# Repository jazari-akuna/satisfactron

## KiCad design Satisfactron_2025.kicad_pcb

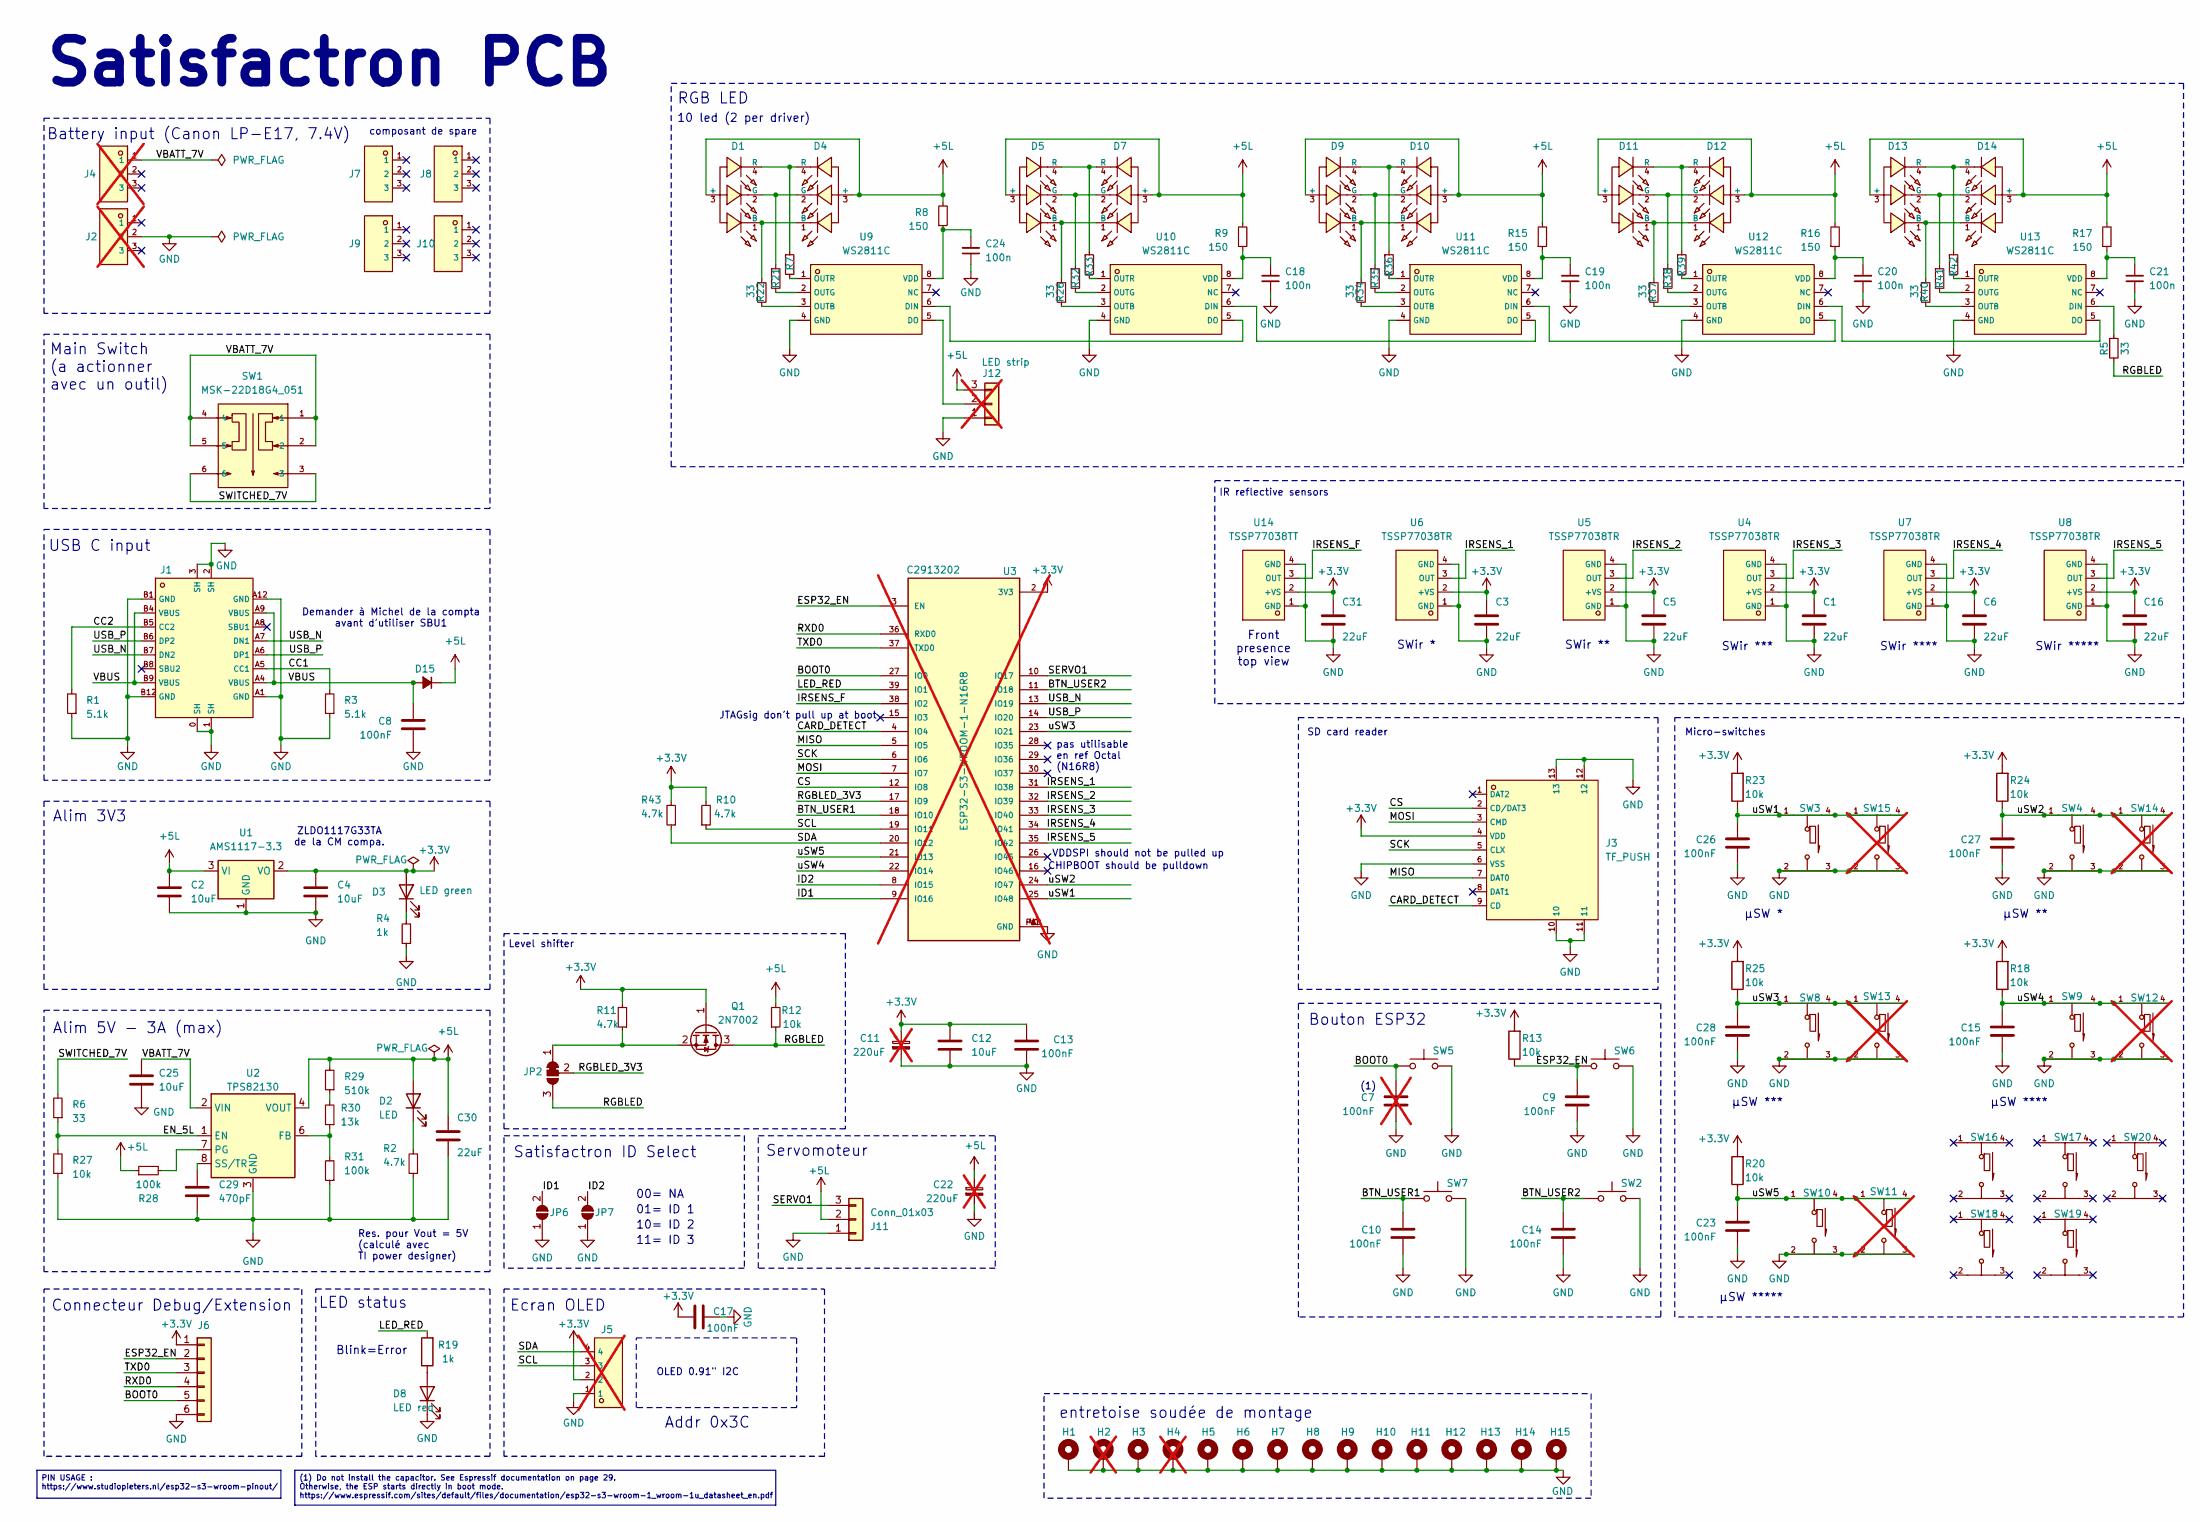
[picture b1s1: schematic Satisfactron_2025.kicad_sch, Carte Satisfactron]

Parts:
C1, C3, C5, C6, C16, C30, C31: 22uF; C_0805_2012Metric; LCSC C45783
C2, C4, C12, C25: 10uF; C_0805_2012Metric; LCSC C440198
C7: 100nF; C_0603_1608Metric_Pad1.08x0.95mm_HandSolder; LCSC C14663; not fitted
C8, C9, C10, C13, C14, C15, C17, C23, C26, C27, C28: 100nF; C_0603_1608Metric_Pad1.08x0.95mm_HandSolder; LCSC C14663
C11, C22: 220uF; C_Radial_D6.3mm_H11.0mm_P2.50mm; not fitted
C18, C19, C20, C21, C24: 100n; C_0603_1608Metric_Pad1.08x0.95mm_HandSolder; LCSC C14663
C29: 470pF; C_0603_1608Metric; LCSC C1620
D1, D4, D5, D7, D9, D10, D11, D12, D13, D14: XL-3210RGBC-YG; LED-ARRAY-SMD_HS-1204-RGB; LCSC C965884
D2: LED; LED_0603_1608Metric; LCSC C2290
D3: LED green; LED_0603_1608Metric; LCSC C2290
D8: LED red; LED_0603_1608Metric; LCSC C2286
D15: 1N4148W; D_SOD-123F; LCSC C81598
H1, H3, H5, H6, H7, H8, H9, H10, H11, H12, H13, H14, H15: SMTSO3040CTJ; SMD-1_BD5.5-D4.0; LCSC C2915635
H2, H4: SMTSO3040CTJ; SMD-1_BD5.5-D4.0; LCSC C2915635; not fitted
J1: USB-TYPE-C-018; USB-C_SMD-TYPE-C-31-M-12; LCSC C2927038
J2, J4: GT-BTP30002-0350B-019B; CONN-SMD_GT-BTP30002-0350B-019B; LCSC C41378766; not fitted
J3: TF_PUSH; TF-SMD_TF-PUSH; LCSC C393941
J5: PZ254V-11-04P_C2691448; Waveshare_screen_0.9; LCSC C2691448; not fitted
J6: Conn_01x06; PinHeader_1x06_P2.54mm_Vertical
J7, J8, J9, J10: GT-BTP30002-0350B-019B; CONN-SMD_GT-BTP30002-0350B-019B; LCSC C41378766
J11: Conn_01x03; PinHeader_1x03_P2.54mm_Vertical
J12: LED strip; PinHeader_1x03_P2.54mm_Vertical; not fitted
JP2: SolderJumper_3_Bridged12; SolderJumper-3_P1.3mm_Bridged12_RoundedPad1.0x1.5mm
JP6: ID1; SolderJumper-2_P1.3mm_Open_RoundedPad1.0x1.5mm
JP7: ID2; SolderJumper-2_P1.3mm_Open_RoundedPad1.0x1.5mm
Q1: 2N7002; SOT-23_Handsoldering; LCSC C8545
R1, R3: 5.1k; R_0603_1608Metric; LCSC C23186
R2, R10, R11, R43: 4.7k; R_0603_1608Metric; LCSC C23162
R4: 1k; R_0603_1608Metric; LCSC C21190
R5, R6, R7, R21, R22, R26, R32, R33, R34, R35, R36, R37, R38, R39, R40, R41, R42: 33; R_0603_1608Metric; LCSC C23140
R8, R9, R15, R16, R17: 150; R_0603_1608Metric; LCSC C22808
R12, R27: 10k; R_0603_1608Metric; LCSC C25804
R13, R18, R20, R23, R24, R25: 10k; R_0603_1608Metric_Pad0.98x0.95mm_HandSolder; LCSC C25804
R19: 1k; R_0603_1608Metric_Pad0.98x0.95mm_HandSolder; LCSC C21190
R28, R31: 100k; R_0603_1608Metric; LCSC C25803
R29: 510k; R_0603_1608Metric; LCSC C23192
R30: 13k; R_0603_1608Metric; LCSC C22797
SW1: MSK-22D18G4_051; SW-TH_HX-MSK-22D18G4-051; LCSC C7507433
SW2, SW5, SW6, SW7: TS-1088-AR02016; SW-SMD_L3.9-W3.0-P4.45; LCSC C720477
SW3, SW4, SW8, SW9, SW10, SW16, SW17, SW18, SW19, SW20: SPVN310101; SW-SMD_SPVN310101; LCSC C255568
SW11, SW12, SW13, SW14, SW15: SPVN310101; SW-SMD_SPVN310101; LCSC C255568; not fitted
U1: AMS1117-3.3; SOT-223-3_TabPin2; LCSC C6186
U2: TPS82130; USIP-8_L3.0-W2.8-P0.65-TL-EP; LCSC C473914
U3: ESP32-S3-WROOM-1-N16R8; WIRELM-SMD_ESP32-S3-WROOM-1; PARTREV v1.0; LCSC C2913202; not fitted
U4, U5, U6, U7, U8: TSSP77038TR; SENSOR-SMD_TSOP75238TR; LCSC C499566
U9, U10, U11, U12, U13: WS2811C; SOP-8_L4.9-W3.9-P1.27-LS6.0-BL; LCSC C2920043
U14: TSSP77038TT; Top-view-TSSP770_SMD_TSOP75238TR; LCSC C3742899

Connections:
+3.3V: C1.1, C3.1, C4.1, C5.1, C6.1, C11.1, C12.1, C13.1, C16.1, C17.1, C31.1, D3.2 (A), J3.4 (VDD), J5.2, J6.1, Q1.1 (G), R10.2, R11.2, R13.2, R18.2, R20.2, R23.2, R24.2, R25.2, R43.2, U1.2 (VO), U3.2 (3V3), U4.2 (+VS), U5.2 (+VS), U6.2 (+VS), U7.2 (+VS), U8.2 (+VS), U14.2 (+VS); also elsewhere on the board
+5L: C2.1, C22.1, C30.1, D1.3 (+), D2.2 (A), D4.3 (+), D5.3 (+), D7.3 (+), D9.3 (+), D10.3 (+), D11.3 (+), D12.3 (+), D13.3 (+), D14.3 (+), D15.1 (K), J11.2, J12.3, R8.2, R9.2, R12.2, R15.2, R16.2, R17.2, R28.1, R29.2, U1.3 (VI), U2.4 (VOUT), U2.5 (VOUT)
/BOOT0: C7.1, J6.5, SW5.1, U3.27 (IO0)
/BTN_USER1: C10.1, SW7.1, U3.18 (IO10)
/BTN_USER2: C14.1, SW2.1, U3.11 (IO18)
/CARD_DETECT: J3.9 (CD), U3.4 (IO4)
/CC1: J1.A5 (CC1), R3.2
/CC2: J1.B5 (CC2), R1.2
/CS: J3.2 (CD/DAT3), U3.12 (IO8)
/EN_5L: R6.1, R27.2, U2.1 (EN)
/ESP32_EN: C9.1, J6.2, R13.1, SW6.1, U3.3 (EN)
/ID1: JP6.2 (B), U3.9 (IO16)
/ID2: JP7.2 (B), U3.8 (IO15)
/IRSENS_1: U3.31 (IO38), U6.3 (OUT)
/IRSENS_2: U3.32 (IO39), U5.3 (OUT)
/IRSENS_3: U3.33 (IO40), U4.3 (OUT)
/IRSENS_4: U3.34 (IO41), U7.3 (OUT)
/IRSENS_5: U3.35 (IO42), U8.3 (OUT)
/IRSENS_F: U3.38 (IO2), U14.3 (OUT); also elsewhere on the board
/LED_RED: R19.2, U3.39 (IO1)
/MISO: J3.7 (DAT0), U3.5 (IO5)
/MOSI: J3.3 (CMD), U3.7 (IO7)
/RGBLED: JP2.3 (B), Q1.3 (D), R5.2, R12.1
/RGBLED_3V3: JP2.2 (C), U3.17 (IO9)
/RXD0: J6.4, U3.36 (RXD0)
/SCK: J3.5 (CLX), U3.6 (IO6)
/SCL: J5.3, R10.1, U3.19 (IO11)
/SDA: J5.4, R43.1, U3.20 (IO12)
/SERVO1: J11.3, U3.10 (IO17)
/SWITCHED_7V: R6.2, SW1.3, SW1.6
/TXD0: J6.3, U3.37 (TXD0)
/USB_N: J1.A7 (DN1), J1.B7 (DN2), U3.13 (IO19)
/USB_P: J1.A6 (DP1), J1.B6 (DP2), U3.14 (IO20)
/VBATT_7V: C25.1, J4.1, SW1.1, SW1.2, SW1.4, SW1.5, U2.2 (VIN)
/VBUS: C8.1, D15.2 (A), J1.A4 (VBUS), J1.A9 (VBUS), J1.B4 (VBUS), J1.B9 (VBUS)
/uSW1: C26.1, R23.1, SW3.1, SW3.4, SW15.1, SW15.4, U3.25 (IO48)
/uSW2: C27.1, R24.1, SW4.1, SW4.4, SW14.1, SW14.4, U3.24 (IO47)
/uSW3: C28.1, R25.1, SW8.1, SW8.4, SW13.1, SW13.4, U3.23 (IO21)
/uSW4: C15.1, R18.1, SW9.1, SW9.4, SW12.1, SW12.4, U3.22 (IO14)
/uSW5: C23.1, R20.1, SW10.1, SW10.4, SW11.1, SW11.4, U3.21 (IO13)
GND: C1.2, C2.2, C3.2, C4.2, C5.2, C6.2, C7.2, C8.2, C9.2, C10.2, C11.2, C12.2, C13.2, C14.2, C15.2, C16.2, C17.2, C18.1, C19.1, C20.1, C21.1, C22.2, C23.2, C24.1, C25.2, C26.2, C27.2, C28.2, C29.2, C30.2, C31.2, D8.1 (K), H1.1, H2.1, H3.1, H4.1, H5.1, H6.1, H7.1, H8.1, H9.1, H10.1, H11.1, H12.1, H13.1, H14.1, H15.1, J1.0 (SH), J1.1 (SH), J1.2 (SH), J1.3 (SH), J1.A1 (GND), J1.A12 (GND), J1.B1 (GND), J1.B12 (GND), J2.2, J3.6 (VSS), J3.10, J3.11, J3.12, J3.13, J5.1, J6.6, J11.1, J12.1, JP6.1 (A), JP7.1 (A), R1.1, R2.1, R3.1, R4.1, R27.1, R31.1, SW2.2, SW3.2, SW3.3, SW4.2, SW4.3, SW5.2, SW6.2, SW7.2, SW8.2, SW8.3, SW9.2, SW9.3, SW10.2, SW10.3, SW11.2, SW11.3, SW12.2, SW12.3, SW13.2, SW13.3, SW14.2, SW14.3, SW15.2, SW15.3, U1.1 (GND), U2.3 (GND), U2.9 (GND), U3.1 (GND), U3.40 (GND), U3.PAD (GND), U4.1 (GND), U4.4 (GND), U5.1 (GND), U5.4 (GND), U6.1 (GND), U6.4 (GND), U7.1 (GND), U7.4 (GND), U8.1 (GND), U8.4 (GND), U9.4 (GND), U10.4 (GND), U11.4 (GND), U12.4 (GND), U13.4 (GND), U14.1 (GND), U14.4 (GND); also elsewhere on the board
unnamed: D1.1 (B), D4.1 (B), R22.1
unnamed: D1.2 (G), D4.2 (G), R21.1
unnamed: D1.4 (R), D4.4 (R), R7.1
unnamed: D2.1 (K), R2.2
unnamed: D3.1 (K), R4.2
unnamed: D5.1 (B), D7.1 (B), R26.1
unnamed: D5.2 (G), D7.2 (G), R32.1
unnamed: D5.4 (R), D7.4 (R), R33.1
unnamed: D8.2 (A), R19.1
unnamed: D9.1 (B), D10.1 (B), R34.1
unnamed: D9.2 (G), D10.2 (G), R35.1
unnamed: D9.4 (R), D10.4 (R), R36.1
unnamed: D11.1 (B), D12.1 (B), R37.1
unnamed: D11.2 (G), D12.2 (G), R38.1
unnamed: D11.4 (R), D12.4 (R), R39.1
unnamed: D13.1 (B), D14.1 (B), R40.1
unnamed: D13.2 (G), D14.2 (G), R41.1
unnamed: D13.4 (R), D14.4 (R), R42.1
unnamed: J12.2, U9.5 (DO)
unnamed: JP2.1 (A), Q1.2 (S), R11.1
unnamed: R29.1, R30.2
unnamed: R30.1, R31.2, U2.6 (FB)
unnamed: R28.2, U2.7 (PG)
unnamed: C29.1, U2.8 (SS/TR)
unnamed: R22.2, U9.3 (OUTB)
unnamed: R21.2, U9.2 (OUTG)
unnamed: R7.2, U9.1 (OUTR)
unnamed: C24.2, R8.1, U9.8 (VDD)
unnamed: U10.6 (DIN), U11.5 (DO)
unnamed: U9.6 (DIN), U10.5 (DO)
unnamed: R26.2, U10.3 (OUTB)
unnamed: R32.2, U10.2 (OUTG)
unnamed: R33.2, U10.1 (OUTR)
unnamed: C18.2, R9.1, U10.8 (VDD)
unnamed: U11.6 (DIN), U12.5 (DO)
unnamed: R34.2, U11.3 (OUTB)
unnamed: R35.2, U11.2 (OUTG)
unnamed: R36.2, U11.1 (OUTR)
unnamed: C19.2, R15.1, U11.8 (VDD)
unnamed: U12.6 (DIN), U13.5 (DO)
unnamed: R37.2, U12.3 (OUTB)
unnamed: R38.2, U12.2 (OUTG)
unnamed: R39.2, U12.1 (OUTR)
unnamed: C20.2, R16.1, U12.8 (VDD)
unnamed: R5.1, U13.6 (DIN)
unnamed: R40.2, U13.3 (OUTB)
unnamed: R41.2, U13.2 (OUTG)
unnamed: R42.2, U13.1 (OUTR)
unnamed: C21.2, R17.1, U13.8 (VDD)

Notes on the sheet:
µSW **
Servomoteur
SD card reader
µSW ****
CHIPBOOT should be pulldown
Micro-switches
entretoise soudée de montage
LED status
ZLDO1117G33TA de la CM compa.
µSW *****
Blink=Error
Satisfactron PCB
OLED 0.91" I2C
Ecran OLED
Level shifter
SWir **
Demander à Michel de la compta avant d'utiliser SBU1
00= NA
Alim 3V3
SWir *
SWir *****
SWir ****
RGB LED
pas utilisable en ref Octal (N16R8)
µSW *
Connecteur Debug/Extension
Res. pour Vout = 5V (calculé avec TI power designer)
SWir ***
Addr 0x3C
Front presence top view
Battery input (Canon LP-E17, 7.4V)
11= ID 3
Alim 5V - 3A (max)
Main Switch (a actionner avec un outil)
JTAGsig don't pull up at boot
10= ID 2
IR reflective sensors
µSW ***
(1)
USB C input

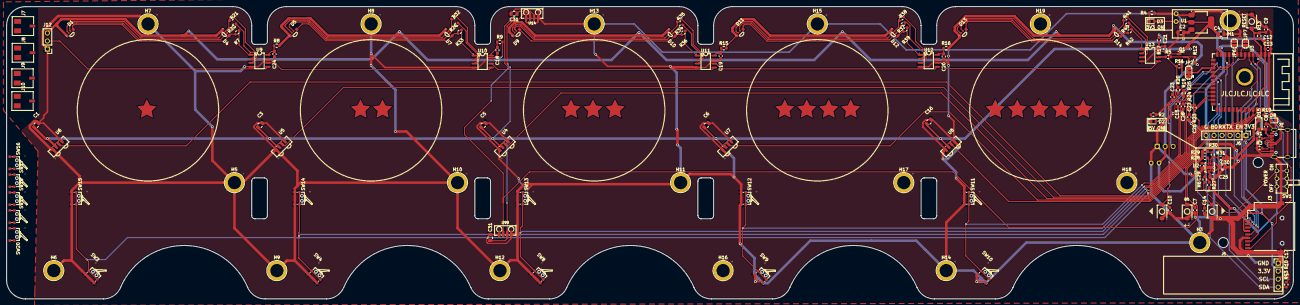
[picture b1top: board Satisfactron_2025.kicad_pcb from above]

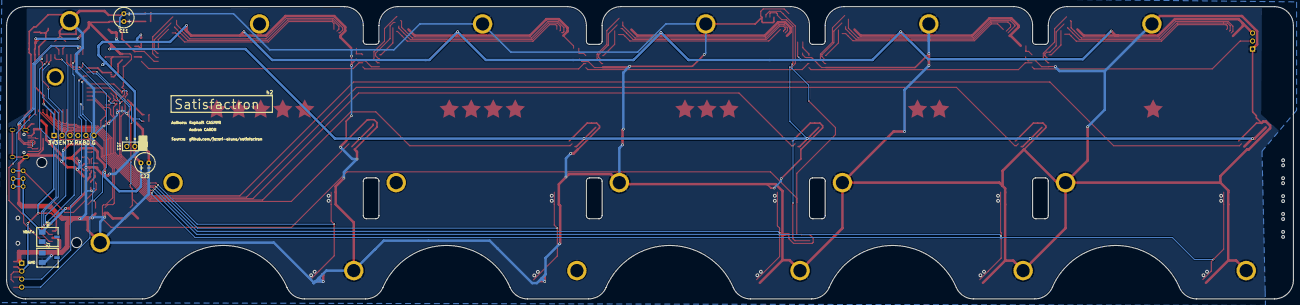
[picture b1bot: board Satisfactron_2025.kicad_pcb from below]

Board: 2 copper layers, 409.5 x 93.0 mm, 156 parts (5 on the bottom side), 90 nets.

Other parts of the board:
C31#2: 22uF; C_0805_2012Metric
H16, H17, H18, H19: SMTSO3040CTJ; SMD-1_BD5.5-D4.0
U99: TSSP77038TT; Top-view-TSSP770_SMD_TSOP75238TR

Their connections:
+3.3V: C31#2.1, U99.2 (+VS); also elsewhere on the board
/IRSENS_F: U99.3 (OUT); also elsewhere on the board
GND: C31#2.2, U99.1 (GND), U99.4 (GND); also elsewhere on the board

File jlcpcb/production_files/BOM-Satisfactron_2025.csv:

Comment,Designator,Footprint,LCSC,Quantity
100nF,"C10,C13,C14,C15,C17,C18,C19,C20,C21,C23,C24,C26,C27,C28,C8,C9",C_0603_1608Metric_Pad1.08x0.95mm_HandSolder,C14663,16
470pF,C29,C_0603_1608Metric,C1620,1
1k,"R19,R4",R_0603_1608Metric_Pad0.98x0.95mm_HandSolder,C21190,2
13k,R30,R_0603_1608Metric,C22797,1
150,"R15,R16,R17,R8,R9",R_0603_1608Metric,C22808,5
LED red,D8,LED_0603_1608Metric,C2286,1
LED,"D2,D3",LED_0603_1608Metric,C2290,2
33,"R21,R22,R26,R32,R33,R34,R35,R36,R37,R38,R39,R40,R41,R42,R5,R6,R7",R_0603_1608Metric,C23140,17
4.7k,"R10,R11,R2,R43",R_0603_1608Metric,C23162,4
5.1k,"R1,R3",R_0603_1608Metric,C23186,2
510k,R29,R_0603_1608Metric,C23192,1
SPVN310101,"SW10,SW16,SW17,SW18,SW19,SW20,SW3,SW4,SW8,SW9",SW-SMD_SPVN310101,C255568,10
100k,"R28,R31",R_0603_1608Metric,C25803,2
10k,"R12,R13,R18,R20,R23,R24,R25,R27",R_0603_1608Metric,C25804,8
SMTSO3040CTJ,"H1,H10,H11,H12,H13,H14,H15,H16,H17,H18,H19,H3,H5,H6,H7,H8,H9",SMD-1_BD5.5-D4.0,C2915635,17
WS2811C,"U10,U11,U12,U13,U9",SOP-8_L4.9-W3.9-P1.27-LS6.0-BL,C2920043,5
USB-TYPE-C-018,J1,USB-C_SMD-TYPE-C-31-M-12,C2927038,1
TSSP77038TT,U14,Top-view-TSSP770_SMD_TSOP75238TR,C3742899,1
TF_PUSH,J3,TF-SMD_TF-PUSH,C393941,1
GT-BTP30002-0350B-019B,"J10,J7,J8,J9",CONN-SMD_GT-BTP30002-0350B-019B,C41378766,4
10uF,"C12,C2,C25,C4",C_0805_2012Metric,C440198,4
22uF,"C1,C16,C3,C30,C5,C6",C_0805_2012Metric,C45783,6
TPS82130,U2,USIP-8_L3.0-W2.8-P0.65-TL-EP,C473914,1
TSSP77038TR,"U4,U5,U6,U7,U8",SENSOR-SMD_TSOP75238TR,C499566,5
AMS1117-3.3,U1,SOT-223-3_TabPin2,C6186,1
TS-1088-AR02016,"SW2,SW5,SW6,SW7",SW-SMD_L3.9-W3.0-P4.45,C720477,4
MSK-22D18G4_051,SW1,SW-TH_HX-MSK-22D18G4-051,C7507433,1
1N4148W,D15,D_SOD-123F,C81598,1
2N7002,Q1,SOT-23,C8545,1
XL-3210RGBC-YG,"D1,D10,D11,D12,D13,D14,D4,D5,D7,D9",LED-ARRAY-SMD_HS-1204-RGB,C965884,10

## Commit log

2025-06-25 creation of schematic draft
2025-06-29 Update footprint and symbol table
2025-06-29 ajout de la mecanique, version draft
2025-06-29 Start populate schematics
2025-06-30 Add DXF, sch placement + start PCB placement
2025-06-30 Continue PCB placement
2025-06-30 avancement schema
2025-06-30 PCB placement 80%
2025-07-01 Schematics done 90% + PCB placement +10%
2025-07-02 Placement done
2025-07-02 Routing 80%
2025-07-02 90% routing
2025-07-02 Routing done, no zones
2025-07-02 assignation JLCPCB
2025-07-02 Minor corrections
2025-07-02 Routing and zones complete, silkscreen in progress
2025-07-02 RC last check, silkscreen done
2025-07-02 JLCPCB assignation
2025-07-02 Stars are shiny now
2025-07-02 Production file (incl. Step)
2025-07-02 ajout CSV
2025-07-02 correction orientation et DNI U99,C31
2025-07-04 Mecanique v2.1
2025-07-04 added STEP
2025-07-04 echantillon tenon-mortaise
2025-07-04 ajout d'echantillon tenon-mortaise
2025-07-12 Add 3D printer plate for 3D printed parts
2025-07-12 Correct major issue on schematics, 5V in missing on 3V3 reg TODO PCB
2025-07-12 Correct corresponding PCB mistake, 5V connected to 3V3 reg now
2025-07-13 added battery holder v1
2025-08-03 maj meca
    correction guide jeton
    mise à jour de la vidange (porte à l'arrière)
    ajout d'un bac de vidange, presentoir
